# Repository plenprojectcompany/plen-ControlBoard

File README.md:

PLEN2 ControlBoard | PLEN Project Company
===============================================================================

## Copyright (c) 2015,
- [Naohiro HAYAISHI](http://earlystone.com/)
- [Mitsuhiro MIYAGUCHI](https://github.com/mitsuhiromiyaguchi)
- [PLEN Project Company Inc.](https://plen.jp)

## Build Environment
- Windows 8.1
- Eagle 6.60

## License
This material is released under the Creative Commons BY 4.0.

**Attention!**  
The schematic diagram of Arduino Micro in schematic file is licensed by Arduino. Please see the detail on their [web-site](https://www.arduino.cc/).
The schematic diagram of Multi-ServoMotor Interface, RS485 communication port and EEPROM is released under Creative Commons Attribution 4.0 International Public License.

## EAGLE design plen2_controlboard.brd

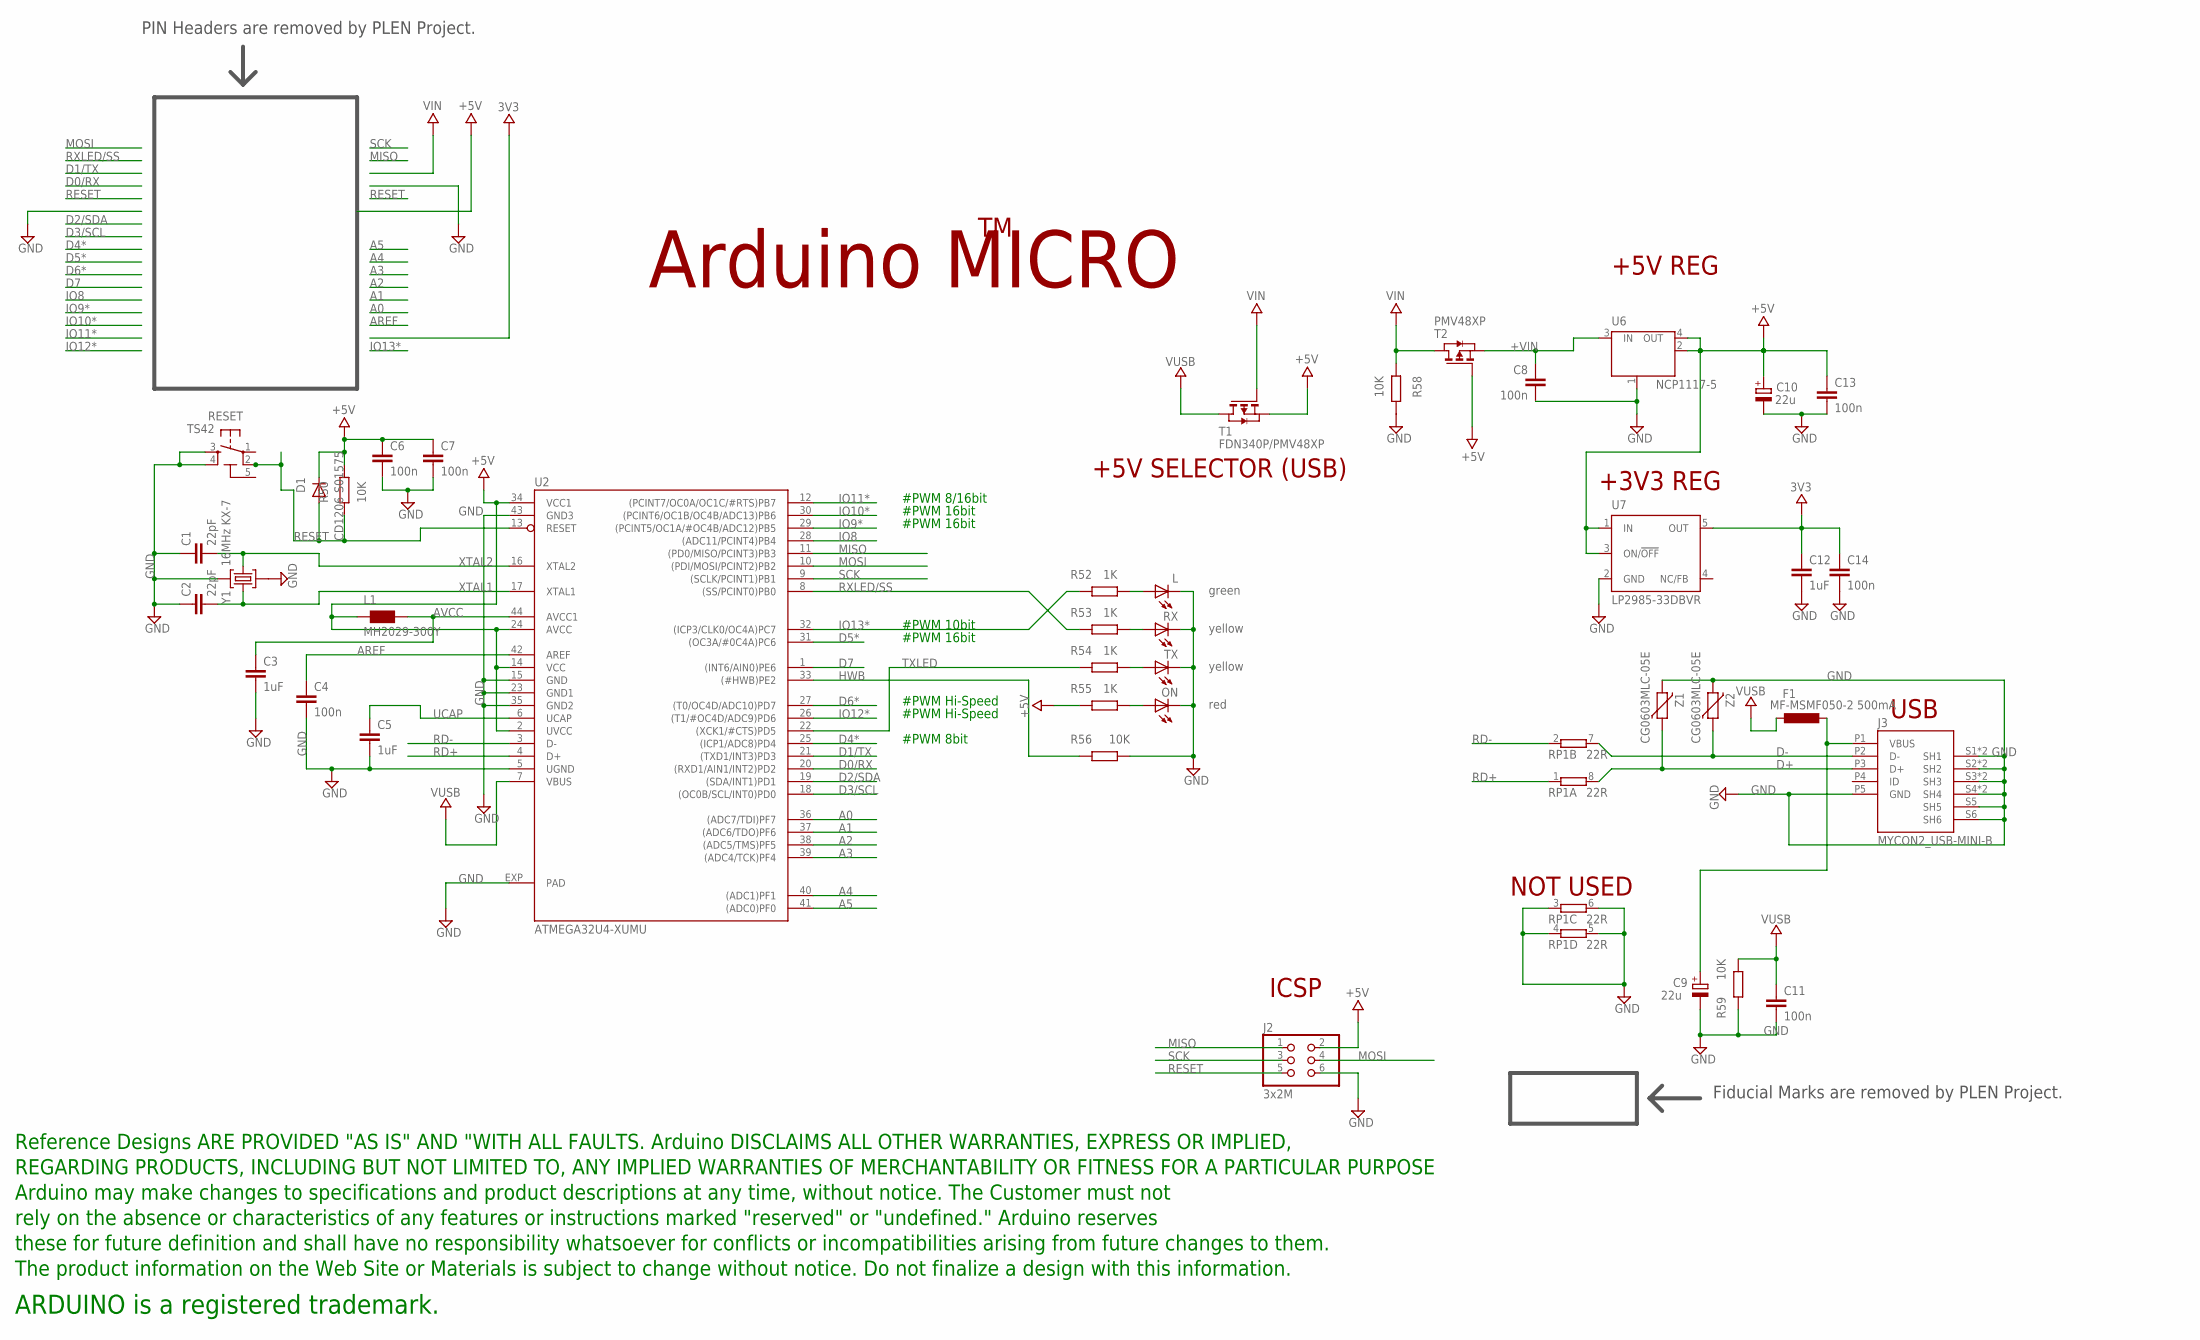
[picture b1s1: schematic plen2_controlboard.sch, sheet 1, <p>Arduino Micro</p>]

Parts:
C1, C2: 22pF; C0402
C3, C5, C12: 1uF; C0402
C4, C6, C7, C8, C11, C13, C14: 100n; C0402
C9, C10: 22u; SMC_B
D1: CD1206-S01575; MINIMELF
F1: MF-MSMF050-2 500mA; L1812
J2: 3x2M; 2X03
J3: MYCON2_USB-MINI-B; CON2_USB_MICRO_B_AT
L: green; CHIPLED_0805
L1: MH2029-300Y; 0805
ON: red; CHIPLED_0805
R50, R56, R58, R59: 10K; R0402
R52, R53, R54, R55: 1K; R0402
RESET: TS42
RP1: 22R; CAY16
RX: yellow; CHIPLED_0805
T1: FDN340P/PMV48XP; SOT-23
T2: PMV48XP; SOT-23
TX: yellow; CHIPLED_0805
U2: ATMEGA32U4-XUMU; QFN44ML7X7
U6: NCP1117-5; LINEAR_SOT223
U7: LP2985-33DBVR; SOT23-DBV
U$3: DISCLAIMER
Y1: 16MHz KX-7; CRYSTAL-3.2-2.5
Z1, Z2: CG0603MLC-05E; CT/CN0603

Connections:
3V3: C12.1, C14.1, U7.5 (OUT); also elsewhere on the board
5-GND: RESET.5 (5-GND)
+5V: C6.1, C7.1, C10.+, C13.1, D1.C, J2.2, L1.1, R50.1, R55.1, T1.2 (S), T2.3 (G), U2.2 (UVCC), U2.14 (VCC), U2.24 (AVCC), U2.34 (VCC1), U6.2 (OUT), U6.4 (OUT), U7.1 (IN), U7.3 (ON/!OFF); also elsewhere on the board
+VIN: C8.1, T2.2 (S), U6.3 (IN)
A0: U2.36 ((ADC7/TDI)PF7)
A1: U2.37 ((ADC6/TDO)PF6)
A2: U2.38 ((ADC5/TMS)PF5)
A3: U2.39 ((ADC4/TCK)PF4)
A4: U2.40 ((ADC1)PF1)
A5: U2.41 ((ADC0)PF0)
AREF: C4.1, U2.42 (AREF)
AVCC: C3.1, L1.2, U2.44 (AVCC1)
D0/RX: U2.20 ((RXD1/AIN1/INT2)PD2); also elsewhere on the board
D1/TX: U2.21 ((TXD1/INT3)PD3); also elsewhere on the board
D2/SDA: U2.19 ((SDA/INT1)PD1); also elsewhere on the board
D3/SCL: U2.18 ((OC0B/SCL/INT0)PD0); also elsewhere on the board
D4*: U2.25 ((ICP1/ADC8)PD4); also elsewhere on the board
D5*: U2.31 ((OC3A/#0C4A)PC6); also elsewhere on the board
D6*: U2.27 ((T0/OC4D/ADC10)PD7); also elsewhere on the board
D7: U2.1 ((INT6/AIN0)PE6)
D+: J3.P3 (D+), RP1.8 (2), Z1.1
D-: J3.P2 (D-), RP1.7 (2), Z2.1
GND: C1.1, C2.1, C3.2, C4.2, C5.2, C6.2, C7.2, C8.2, C9.-, C10.-, C11.2, C12.2, C13.2, C14.2, J2.6, J3.P5 (GND), J3.S1 (SH1), J3.S2 (SH2), J3.S3 (SH3), J3.S4 (SH4), J3.S5 (SH5), J3.S6 (SH6), J3.S7 (SH1), J3.S8 (SH2), J3.S9 (SH3), J3.S10 (SH4), L.C, ON.C, R56.2, R58.1, R59.1, RESET.3, RESET.4, RP1.3 (1), RP1.4 (1), RP1.5 (2), RP1.6 (2), RX.C, TX.C, U2.5 (UGND), U2.15 (GND), U2.23 (GND1), U2.35 (GND2), U2.43 (GND3), U2.EXP (PAD), U6.1 (GND/ADJ), U7.2 (GND), Y1.2 (GND), Y1.4 (GND), Z1.2, Z2.2; also elsewhere on the board
HWB: R56.1, U2.33 ((#HWB)PE2)
IO8: U2.28 ((ADC11/PCINT4)PB4)
IO9*: U2.29 ((PCINT5/OC1A/#OC4B/ADC12)PB5); also elsewhere on the board
IO10*: U2.30 ((PCINT6/OC1B/OC4B/ADC13)PB6); also elsewhere on the board
IO11*: U2.12 ((PCINT7/OC0A/OC1C/#RTS)PB7); also elsewhere on the board
IO12*: U2.26 ((T1/#OC4D/ADC9)PD6); also elsewhere on the board
IO13*: R52.1, U2.32 ((ICP3/CLK0/OC4A)PC7)
MISO: J2.1, U2.11 ((PD0/MISO/PCINT3)PB3)
MOSI: J2.4, U2.10 ((PDI/MOSI/PCINT2)PB2)
unnamed: R53.2, RX.A
unnamed: ON.A, R55.2
unnamed: R54.2, TX.A
unnamed: L.A, R52.2
RD+: RP1.1, U2.4 (D+)
RD-: RP1.2 (1), U2.3 (D-)
RESET: D1.A, J2.5, R50.2, RESET.2, U2.13 (RESET); also elsewhere on the board
RXLED/SS: R53.1, U2.8 ((SS/PCINT0)PB0)
SCK: J2.3, U2.9 ((SCLK/PCINT1)PB1)
TXLED: R54.1, U2.22 ((XCK1/#CTS)PD5)
UCAP: C5.1, U2.6 (UCAP)
VIN: R58.2, T1.3 (G), T2.1 (D); also elsewhere on the board
VUSB: C11.1, F1.2, R59.2, T1.1 (D), U2.7 (VBUS)
VUSBD: C9.+, F1.1, J3.P1 (VBUS)
XTAL1: C2.2, U2.17 (XTAL1), Y1.3 (C2)
XTAL2: C1.2, U2.16 (XTAL2), Y1.1 (C1)

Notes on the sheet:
Arduino MICRO
+5V REG
ICSP
USB
+5V SELECTOR (USB)
NOT USED
+3V3 REG
#PWM 8bit
#PWM Hi-Speed
#PWM 16bit
#PWM 10bit
#PWM 8/16bit
Fiducial Marks are removed by PLEN Project.
PIN Headers are removed by PLEN Project.

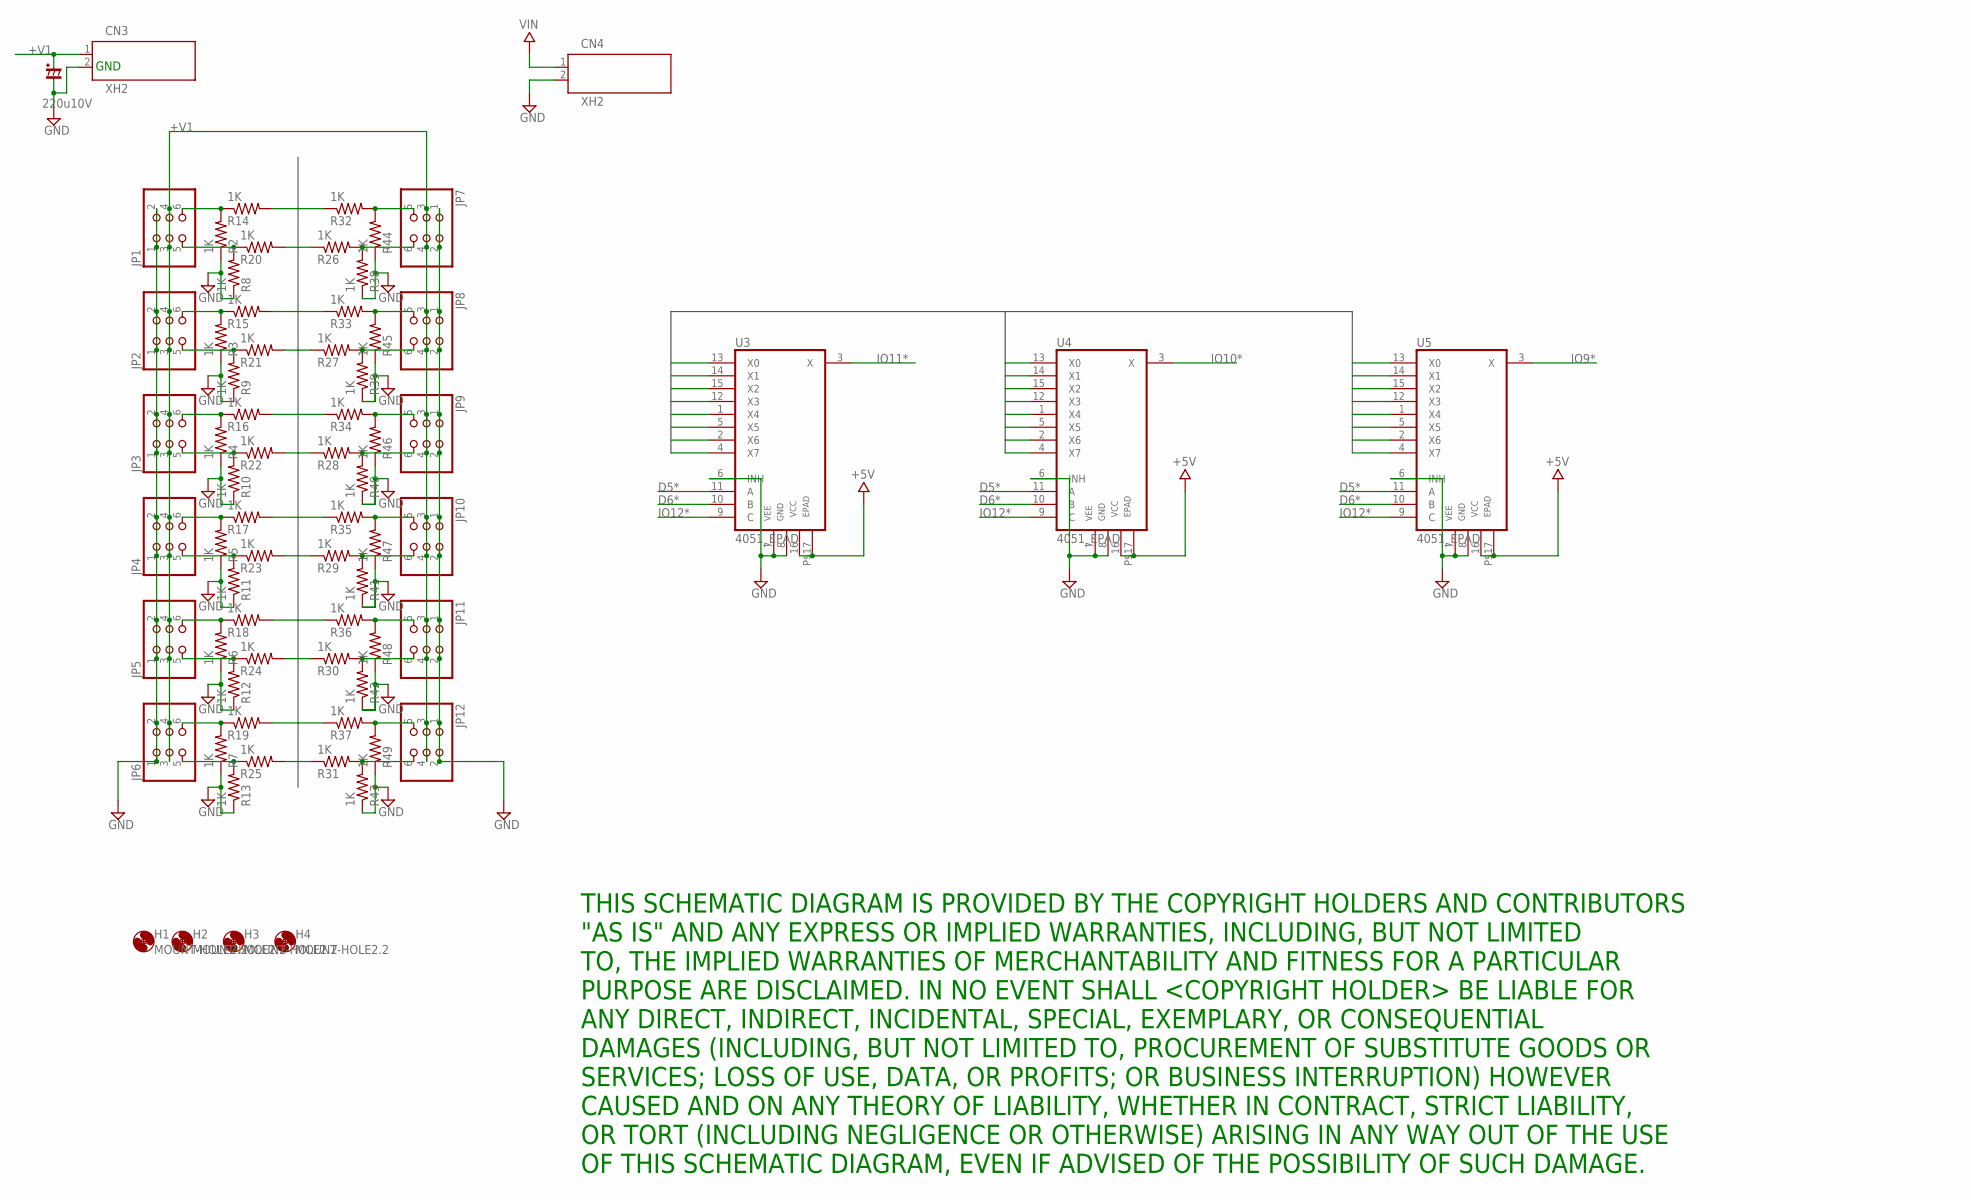
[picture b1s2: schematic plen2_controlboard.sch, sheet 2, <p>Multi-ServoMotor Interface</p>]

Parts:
CN3, CN4: XH2
CP1: 220u10V; CP_S05-05
H1, H2, H3, H4: MOUNT-HOLE2.2; 2,2
JP1, JP2, JP3, JP4, JP5, JP6, JP7, JP8, JP9, JP10, JP11, JP12: PINHD-2X03_2.54; 2X03
R2, R3, R4, R5, R6, R7, R8, R9, R10, R11, R12, R13, R14, R15, R16, R17, R18, R19, R20, R21, R22, R23, R24, R25, R26, R27, R28, R29, R30, R31, R32, R33, R34, R35, R36, R37, R38, R39, R40, R41, R42, R43, R44, R45, R46, R47, R48, R49: 1K; R0402S
U3, U4, U5: 4051_EPAD; SOT763-1

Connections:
+5V: U3.16 (VCC), U3.P$17 (EPAD), U4.16 (VCC), U4.P$17 (EPAD), U5.16 (VCC), U5.P$17 (EPAD); also elsewhere on the board
+V1: CN3.1, CP1.+ (1), JP1.3, JP1.4, JP2.3, JP2.4, JP3.3, JP3.4, JP4.3, JP4.4, JP5.3, JP5.4, JP6.3, JP6.4, JP7.3, JP7.4, JP8.3, JP8.4, JP9.3, JP9.4, JP10.3, JP10.4, JP11.3, JP11.4, JP12.3, JP12.4
D5*: U3.11 (A), U4.11 (A), U5.11 (A); also elsewhere on the board
D6*: U3.10 (B), U4.10 (B), U5.10 (B); also elsewhere on the board
GND: CN3.2, CN4.2, CP1.- (2), JP1.1, JP1.2, JP2.1, JP2.2, JP3.1, JP3.2, JP4.1, JP4.2, JP5.1, JP5.2, JP6.1, JP6.2, JP7.1, JP7.2, JP8.1, JP8.2, JP9.1, JP9.2, JP10.1, JP10.2, JP11.1, JP11.2, JP12.1, JP12.2, R2.1, R3.1, R4.1, R5.1, R6.1, R7.1, R8.1, R9.1, R10.1, R11.1, R12.1, R13.1, R38.1, R39.1, R40.1, R41.1, R42.1, R43.1, R44.1, R45.1, R46.1, R47.1, R48.1, R49.1, U3.6 (INH), U3.7 (VEE), U3.8 (GND), U4.6 (INH), U4.7 (VEE), U4.8 (GND), U5.6 (INH), U5.7 (VEE), U5.8 (GND); also elsewhere on the board
IO9*: U5.3 (X); also elsewhere on the board
IO10*: U4.3 (X); also elsewhere on the board
IO11*: U3.3 (X); also elsewhere on the board
IO12*: U3.9 (C), U4.9 (C), U5.9 (C); also elsewhere on the board
unnamed: JP1.5, R8.2, R20.1
unnamed: JP1.6, R2.2, R14.1
unnamed: JP3.5, R10.2, R22.1
unnamed: JP2.5, R9.2, R21.1
unnamed: JP2.6, R3.2, R15.1
unnamed: JP3.6, R4.2, R16.1
unnamed: JP4.5, R11.2, R23.1
unnamed: JP4.6, R5.2, R17.1
unnamed: JP5.5, R12.2, R24.1
unnamed: JP5.6, R6.2, R18.1
unnamed: JP6.5, R13.2, R25.1
unnamed: JP6.6, R7.2, R19.1
unnamed: JP7.5, R32.2, R44.2
unnamed: JP7.6, R26.2, R38.2
unnamed: JP9.5, R34.2, R46.2
unnamed: JP8.5, R33.2, R45.2
unnamed: JP8.6, R27.2, R39.2
unnamed: JP9.6, R28.2, R40.2
unnamed: JP10.5, R35.2, R47.2
unnamed: JP10.6, R29.2, R41.2
unnamed: JP11.5, R36.2, R48.2
unnamed: JP11.6, R30.2, R42.2
unnamed: JP12.5, R37.2, R49.2
unnamed: JP12.6, R31.2, R43.2
SRV0: R14.2, U3.13 (X0)
SRV1: R20.2, U3.14 (X1)
SRV2: R15.2, U3.15 (X2)
SRV3: R21.2, U3.12 (X3)
SRV4: R16.2, U3.1 (X4)
SRV5: R22.2, U3.5 (X5)
SRV6: R17.2, U3.2 (X6)
SRV7: R23.2, U3.4 (X7)
SRV8: R18.2, U4.13 (X0)
SRV9: R24.2, U4.14 (X1)
SRV10: R19.2, U4.15 (X2)
SRV11: R25.2, U4.12 (X3)
SRV12: R32.1, U4.1 (X4)
SRV13: R26.1, U4.5 (X5)
SRV14: R33.1, U4.2 (X6)
SRV15: R27.1, U4.4 (X7)
SRV16: R34.1, U5.13 (X0)
SRV17: R28.1, U5.14 (X1)
SRV18: R35.1, U5.15 (X2)
SRV19: R29.1, U5.12 (X3)
SRV20: R36.1, U5.1 (X4)
SRV21: R30.1, U5.5 (X5)
SRV22: R37.1, U5.2 (X6)
SRV23: R31.1, U5.4 (X7)
VIN: CN4.1; also elsewhere on the board

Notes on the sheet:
GND
THIS SCHEMATIC DIAGRAM IS PROVIDED BY THE COPYRIGHT HOLDERS AND CONTRIBUTORS "AS IS" AND ANY EXPRESS OR IMPLIED WARRANTIES, INCLUDING, BUT NOT LIMITED TO, THE IMPLIED WARRANTIES OF MERCHANTABILITY AND FITNESS FOR A PARTICULAR PURPOSE ARE DISCLAIMED. IN NO EVENT SHALL <COPYRIGHT HOLDER> BE LIABLE FO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

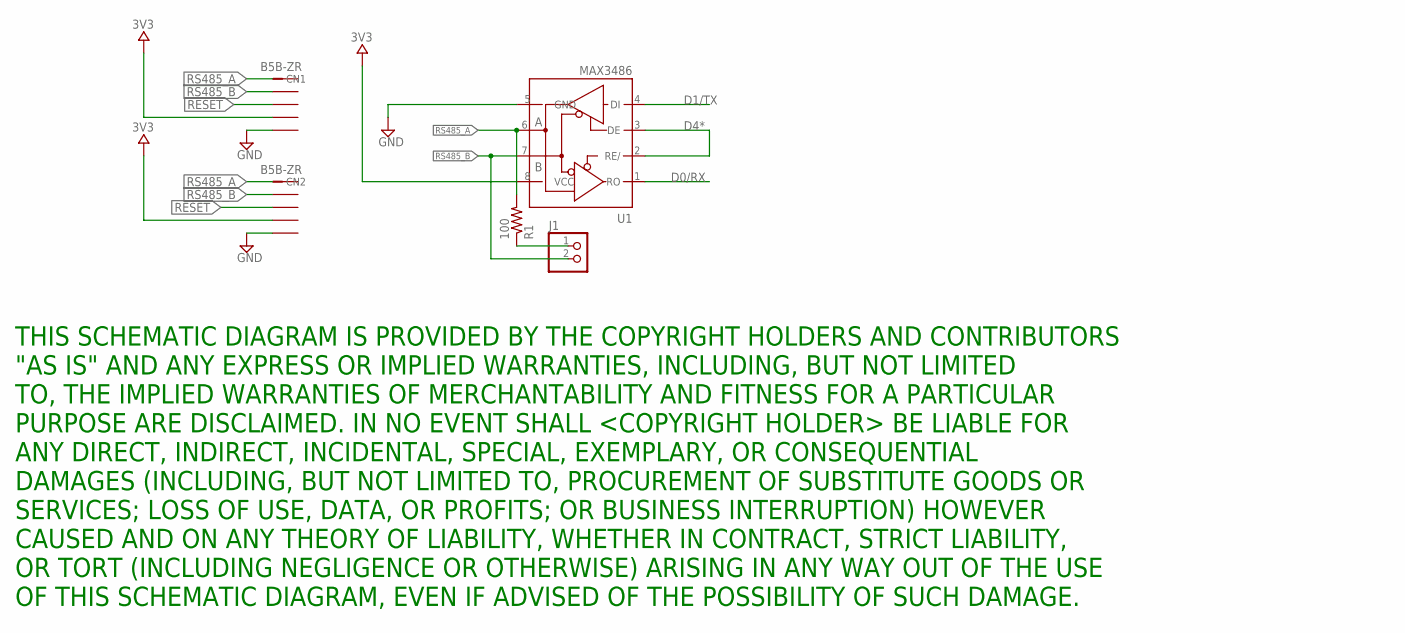
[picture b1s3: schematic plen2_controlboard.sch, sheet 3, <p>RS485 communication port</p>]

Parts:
CN1, CN2: B5B-ZR
J1: PINHD-1X2; 1X02
R1: 100; R0402S
U1: MAX3486; SO08

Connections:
3V3: CN1.4, CN2.4, U1.8 (VCC); also elsewhere on the board
D0/RX: U1.1 (RO); also elsewhere on the board
D1/TX: U1.4 (DI); also elsewhere on the board
D4*: U1.2 (RE/), U1.3 (DE); also elsewhere on the board
GND: CN1.5, CN2.5, U1.5 (GND); also elsewhere on the board
unnamed: J1.1, R1.1
RESET: CN1.3, CN2.3; also elsewhere on the board
RS485_A: CN1.1, CN2.1, R1.2, U1.6 (A)
RS485_B: CN1.2, CN2.2, J1.2, U1.7 (B)

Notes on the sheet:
THIS SCHEMATIC DIAGRAM IS PROVIDED BY THE COPYRIGHT HOLDERS AND CONTRIBUTORS "AS IS" AND ANY EXPRESS OR IMPLIED WARRANTIES, INCLUDING, BUT NOT LIMITED TO, THE IMPLIED WARRANTIES OF MERCHANTABILITY AND FITNESS FOR A PARTICULAR PURPOSE ARE DISCLAIMED. IN NO EVENT SHALL <COPYRIGHT HOLDER> BE LIABLE FO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

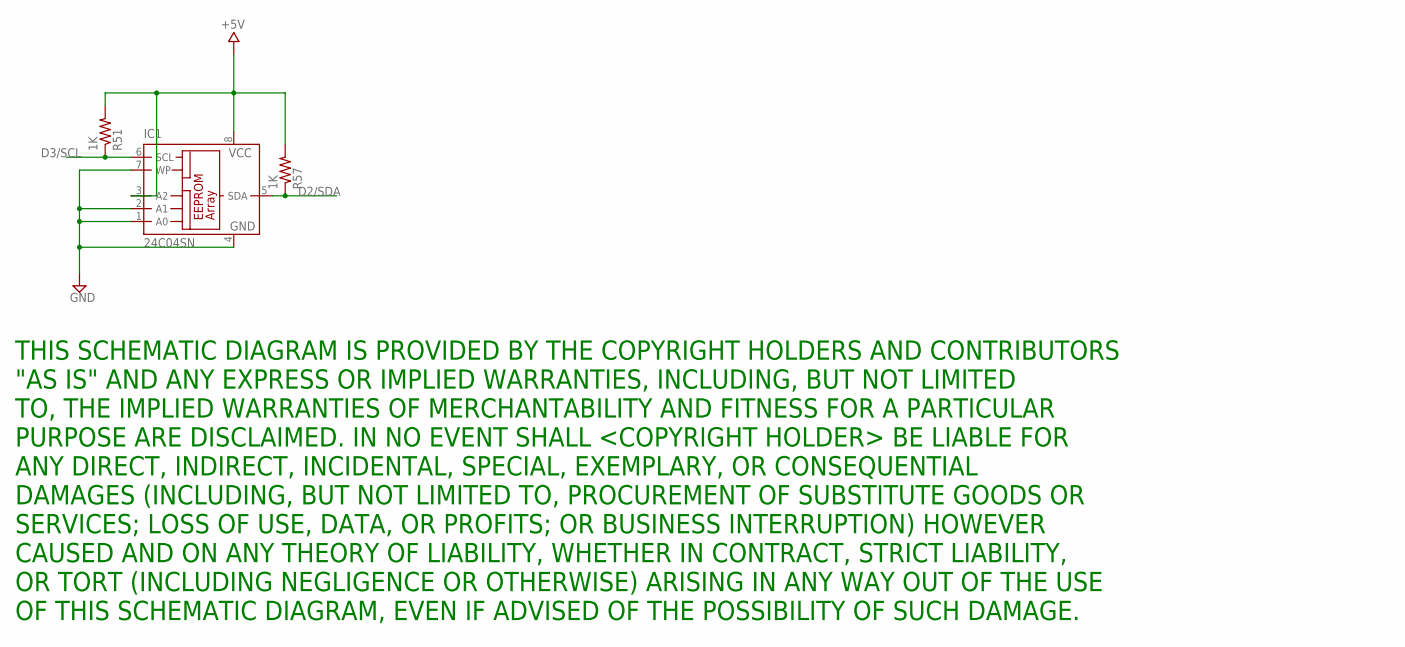
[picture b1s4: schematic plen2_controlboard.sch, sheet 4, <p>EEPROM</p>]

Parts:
IC1: 24C04SN; SO-08
R51, R57: 1K; R0402S

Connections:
+5V: IC1.3 (A2), IC1.8 (VCC), R51.2, R57.2; also elsewhere on the board
D2/SDA: IC1.5 (SDA), R57.1; also elsewhere on the board
D3/SCL: IC1.6 (SCL), R51.1; also elsewhere on the board
GND: IC1.1 (A0), IC1.2 (A1), IC1.4 (GND), IC1.7 (WP); also elsewhere on the board

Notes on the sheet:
THIS SCHEMATIC DIAGRAM IS PROVIDED BY THE COPYRIGHT HOLDERS AND CONTRIBUTORS "AS IS" AND ANY EXPRESS OR IMPLIED WARRANTIES, INCLUDING, BUT NOT LIMITED TO, THE IMPLIED WARRANTIES OF MERCHANTABILITY AND FITNESS FOR A PARTICULAR PURPOSE ARE DISCLAIMED. IN NO EVENT SHALL <COPYRIGHT HOLDER> BE LIABLE FO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

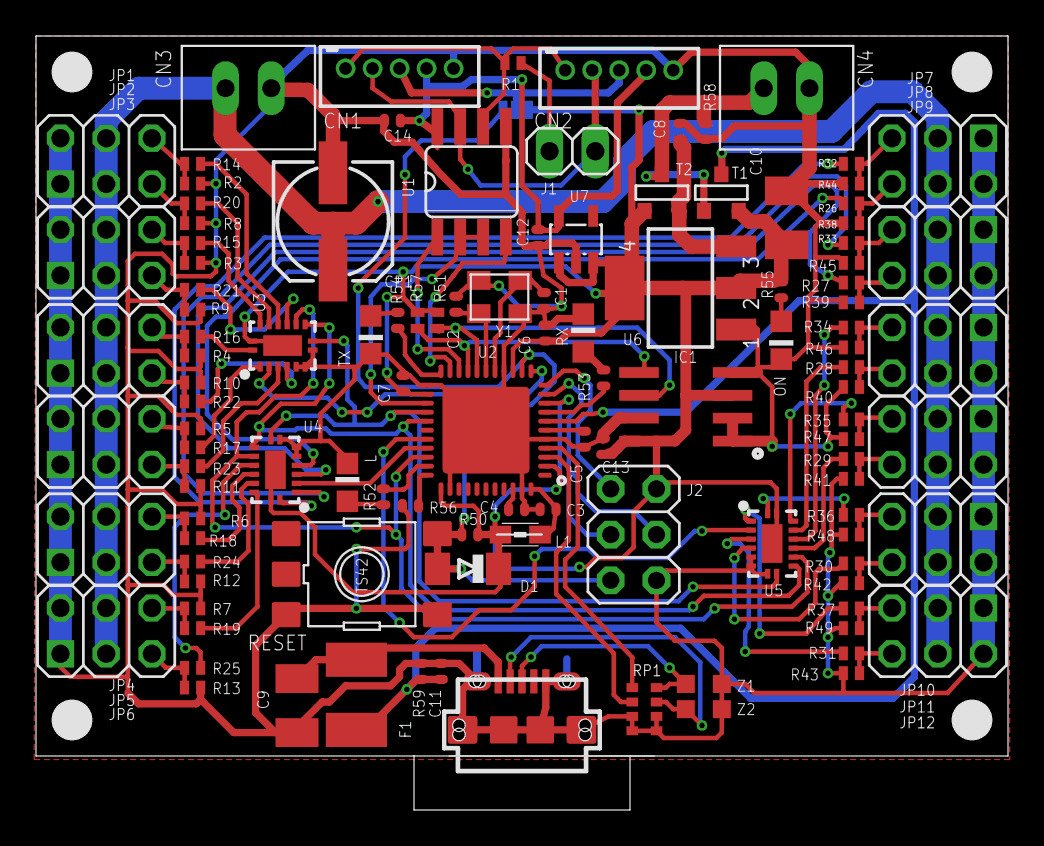
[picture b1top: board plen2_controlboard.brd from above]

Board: 2 copper layers, 54.0 x 43.0 mm, 120 parts (0 on the bottom side), 91 nets.

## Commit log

2015-08-31 Added eagle files.
2015-08-31 Fix LICENSE.md and README.md.
2016-03-21 Fix file-names & documents
2016-03-21 Fix miss-spelling
2016-04-14 Fix company information
2016-07-27 Fix power line
